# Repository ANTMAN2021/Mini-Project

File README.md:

# Mini-Project
Repository for third year mini project

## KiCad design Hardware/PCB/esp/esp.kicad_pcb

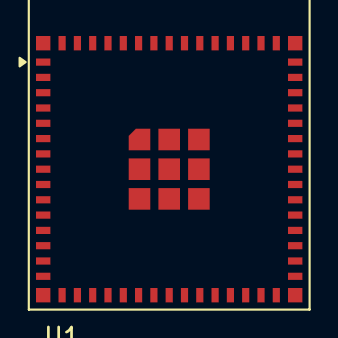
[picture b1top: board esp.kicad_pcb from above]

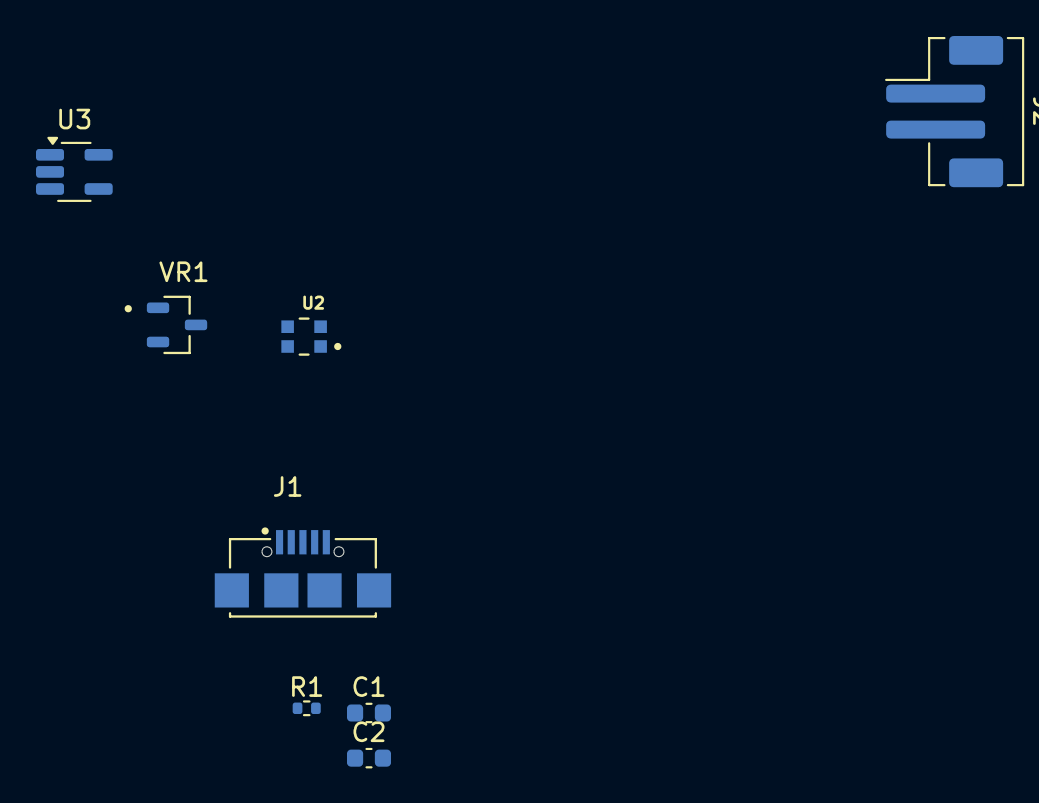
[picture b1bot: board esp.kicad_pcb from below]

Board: 2 copper layers, 9 parts (8 on the bottom side), 6 nets, no tracks yet.

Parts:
C1, C2: 4.7uF/0603; C_0603_1608Metric
J1: UJ2-MIBH-G-SMT-TR; CUI_UJ2-MIBH-G-SMT-TR
J2: Conn_01x02_MountingPin; JST_PH_B2B-PH-SM4-TB_1x02-1MP_P2.00mm_Vertical
R1: 2K/0402; R_0402_1005Metric
U1: ESP32-S3-MINI-1; ESP32-S2-MINI-1
U2: WS2812-2020; LED_WS2812-2020
U3: MCP73831-2-OT; SOT-23-5_HandSoldering
VR1: TLV76050DBZT; SOT95P237X112-3N

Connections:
/power/+VBAT: C1.1, U3.3 (V_{BAT})
/power/V_USB: C2.1, U3.4 (V_{DD})
GND: C1.2, C2.2, J2.2, J2.MP (MountPin), R1.2, U3.2 (V_{SS})
unnamed: J1.S1 (SHIELD), J1.S2 (SHIELD), J1.S3 (SHIELD), J1.S4 (SHIELD)
unnamed: U1.1 (GND), U1.2 (GND), U1.42 (GND), U1.43 (GND), U1.46 (GND), U1.47 (GND), U1.48 (GND), U1.49 (GND), U1.50 (GND), U1.51 (GND), U1.52 (GND), U1.53 (GND), U1.54 (GND), U1.55 (GND), U1.56 (GND), U1.57 (GND), U1.58 (GND), U1.59 (GND), U1.60 (GND), U1.61 (GND), U1.62 (GND), U1.63 (GND), U1.64 (GND), U1.65 (GND)
unnamed: R1.1, U3.5 (PROG)

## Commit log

2025-01-11 Create Arnav
2025-01-11 Create PCB
2025-01-11 Create PCB Files
2025-01-19 ESP32_S3_MINI PCB
    PCB with inner radius
